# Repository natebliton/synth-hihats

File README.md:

# synth-hihats

Basic implementation of an analog hihat circuit, basic VCA on a noise signal.

I don't like this one very much, and will probably re-do with this, or a modification of it: https://electro-music.com/forum/viewtopic.php?t=55928

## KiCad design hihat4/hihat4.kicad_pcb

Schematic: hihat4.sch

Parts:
C1: 100nF; C_Disc_D6.0mm_W2.5mm_P5.00mm
C2: 2.2uF; CP_Radial_D5.0mm_P2.50mm
C3, C4: 100pF; C_Disc_D6.0mm_W2.5mm_P5.00mm
C5: 0.47uF; C_Disc_D6.0mm_W2.5mm_P5.00mm
C6: 470pF; C_Disc_D6.0mm_W2.5mm_P5.00mm
C7: 0.1uF; C_Disc_D6.0mm_W2.5mm_P5.00mm
C8: 100uF; CP_Radial_D5.0mm_P2.50mm
C9: 10nF; C_Disc_D6.0mm_W2.5mm_P5.00mm
C10, C11: 220nF; C_Disc_D6.0mm_W2.5mm_P5.00mm
C12: 4.7uF; CP_Radial_D5.0mm_P2.50mm
D1, D2, D3: 1N4148; D_DO-35_SOD27_P7.62mm_Horizontal
J1, J2: Input; PinHeader_1x02_P2.54mm_Vertical
J3: Output; PinHeader_1x02_P2.54mm_Vertical
J4: Power; PinHeader_1x03_P2.54mm_Vertical
Q1: BC548; TO-92_Inline
Q2: 2N3904; TO-92_Inline
R1, R8, R9, R10, R12: 100k; R_Axial_DIN0207_L6.3mm_D2.5mm_P10.16mm_Horizontal
R2, R4: 47k; R_Axial_DIN0207_L6.3mm_D2.5mm_P10.16mm_Horizontal
R5: 1K; R_Axial_DIN0207_L6.3mm_D2.5mm_P10.16mm_Horizontal
R6: 10k; R_Axial_DIN0207_L6.3mm_D2.5mm_P10.16mm_Horizontal
R7: 4.7k; R_Axial_DIN0207_L6.3mm_D2.5mm_P10.16mm_Horizontal
R11, R13: 2.2k; R_Axial_DIN0207_L6.3mm_D2.5mm_P10.16mm_Horizontal
R14: 1M; R_Axial_DIN0207_L6.3mm_D2.5mm_P10.16mm_Horizontal
RV1: 1M; PinHeader_1x03_P2.54mm_Vertical
U1: TL074; DIP-14_W7.62mm_Socket

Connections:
+12V: C4.2, J4.1, R7.1, R14.1, U1.4 (V+)
-12V: C3.1, J4.3, U1.11 (V-)
GND: C1.1, C2.2, C3.2, C4.1, C6.1, C8.2, C10.2, C11.2, J1.2, J2.2, J3.2, J4.2, Q1.2 (B), Q2.1, R1.2, R9.2, RV1.1, RV1.2, U1.10 (+), U1.12 (+)
unnamed: C1.2, D2.1, R2.2
unnamed: C2.1, D3.1, R4.1
unnamed: C5.1, Q2.2, R14.2
unnamed: C5.2, R12.1, U1.1
unnamed: C6.2, D1.1, Q2.3
unnamed: C7.1, R5.2
unnamed: C7.2, D1.2, R2.1, R4.2
unnamed: C8.1, R7.2, R8.1
unnamed: C9.1, R9.1, U1.5 (+)
unnamed: C9.2, Q1.3 (E), R8.2
unnamed: C10.1, R11.2
unnamed: C11.1, R13.2
unnamed: C12.1, R6.1, U1.8
unnamed: C12.2, J3.1
unnamed: D2.2, J2.1, R1.1
unnamed: D3.2, J1.1, RV1.3
unnamed: R5.1, R6.2, U1.9 (-)
unnamed: R10.1, U1.3 (+), U1.7
unnamed: R10.2, R11.1, U1.6 (-)
unnamed: R12.2, R13.1, U1.2 (-)
unnamed: U1.13 (-), U1.14

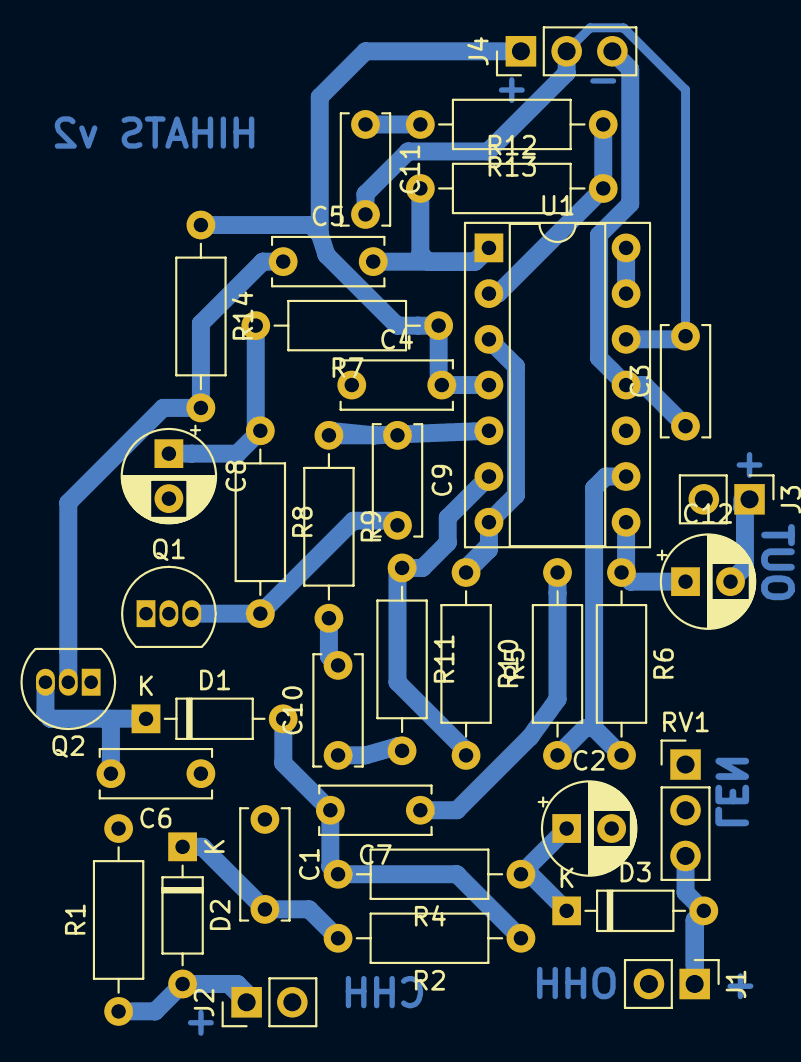
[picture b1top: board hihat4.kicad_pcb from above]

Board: 2 copper layers, 36 parts (0 on the bottom side), 24 nets.

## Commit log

2020-11-29 laied out v4
2020-11-29 adjusted output gain 10x, shortened CHH
